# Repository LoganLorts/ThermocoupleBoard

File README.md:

Current iteration uses an Arduino giga with an arduino mega data shield communicating with the LTC2984.
Links:
https://www.analog.com/en/products/ltc2984.html
https://store-usa.arduino.cc/products/giga-r1-wifi?srsltid=AfmBOopj3Obfn5Uupg23lJG5jRPGHVTn0Cs4W42ruEa2sTFBW0iU7hsE
https://learn.adafruit.com/adafruit-data-logger-shield/overview
https://www.analog.com/en/resources/evaluation-hardware-and-software/evaluation-boards-kits/dc2420a.html#eb-overview (demo board)

To Do:

Software:
All software currently made for demo board, once the new LTC2984 (thermocouple board) is completed, adapt code.

harmonic boundry heating:
test heating accuracy
test acquisition rate
test timing of loop
parallelize processes
make LTC get measurements while the rest of the loop runs

ATMC LTC2984:
test heating accuracy
test acquisition rate
test timing of loop
parallelize processes
make LTC get measurements while the rest of the loop runs

Hardware:

Thermocouple board:
Test functionality and accuracy
solder termblocks

Heating Board:
order and solder logic inverters
order and solder optoisolaters
order and solder heating termblocks
testing

giga hat:
(if needed) Once thermocouple and heating board are tested, make giga hat for SD card reader, mosfet drives, thermocouple SPI connections, humidity sensor, and pressure sensor

Demo board:
Order and solder 2 of the remaining heating termblocks and mosfet drivers (currently one working)
3d print case
rewire to clean setup around the case
(optional) Add barrel jack connector for power

Notes:

Demo board notes:
mosfet driver pin: pin 8
LTC chip select pin: pin 7
SD card reader chip select: pin 10
Power from DC power supply up to 15V
serial speed: 115200
Cold junction sensor avaliable on channel 1 and channel 2 (only need one)
Differential thermocouple readings, select higher channel with differential setting; the postive lead goes to the higher channel and negative lead to one channel lower.
Intented to run up to 9 thermocouples with 3 mosfet drivers runnning the heating element.
Real time clock is I2C on wire 1 (address 0x68)
cold junction sensor is an npn BJT shorted to function as a diode, the ideality factor can be changed to reflect this, but default works.

SPI connections are shown here, ribbon cable connector is not used with the giga. 

Heating board notes:
rated 15V 10 Amps (realistically no more than 5 amps with 3 drivers on)
Do not common ground with the giga

Thermocouple board notes:
Cold junction sensor avaliable on channel 20 and channel 9. Use channel 20 to normalize channels 14-19, channel 9 for the rest.
Intended to run 18 thermocouples, single ended mode (thermocouples go channel to ground)
cold junction sensor is an npn BJT shorted to function as a diode, the ideality factor can be changed to reflect this, but default works.

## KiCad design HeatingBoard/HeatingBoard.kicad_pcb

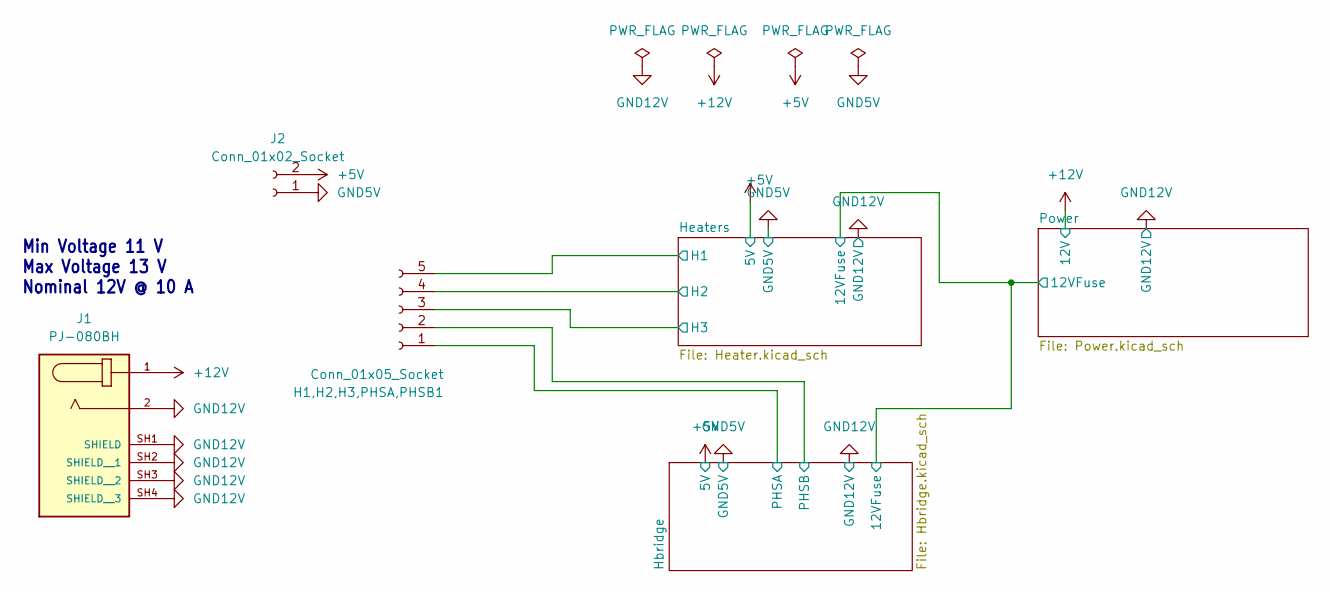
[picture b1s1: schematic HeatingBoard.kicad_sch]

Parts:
H1,H2,H3,PHSA,PHSB1: Conn_01x05_Socket; PinHeader_1x05_P2.54mm_Vertical
J1: PJ-080BH; CUI_PJ-080BH; PARTREV 1.04
J2: Conn_01x02_Socket; PinHeader_1x02_P2.54mm_Vertical

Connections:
+5V: J2.2; also elsewhere on the board
+12V: J1.1; also elsewhere on the board
/Hbridge/PHSA: H1,H2,H3,PHSA,PHSB1.1; also elsewhere on the board
/Hbridge/PHSB: H1,H2,H3,PHSA,PHSB1.2; also elsewhere on the board
/Heaters/H1: H1,H2,H3,PHSA,PHSB1.5; also elsewhere on the board
/Heaters/H2: H1,H2,H3,PHSA,PHSB1.4; also elsewhere on the board
/Heaters/H3: H1,H2,H3,PHSA,PHSB1.3; also elsewhere on the board
GND5V: J2.1; also elsewhere on the board
GND12V: J1.2, J1.SH1 (SHIELD), J1.SH2 (SHIELD__1), J1.SH3 (SHIELD__2), J1.SH4 (SHIELD__3); also elsewhere on the board

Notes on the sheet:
Min Voltage 11 V Max Voltage 13 V Nominal 12V @ 10 A

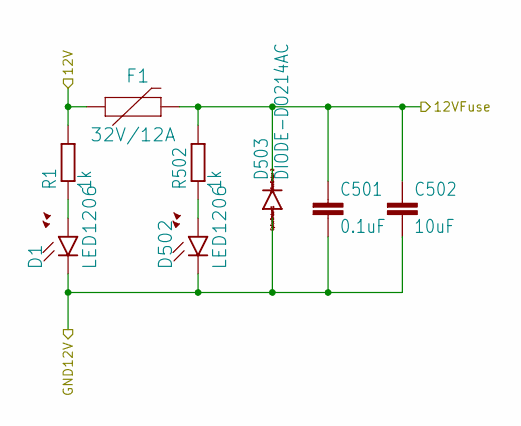
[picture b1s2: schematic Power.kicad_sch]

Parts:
C501: 0.1uF; C1206
C502: 10uF; C1206
D1, D502: LED1206; LED-1206
D503: DIODE-DO214AC; DO214AC_210; DIGI-PN SMAZ15-TPMSCT-ND
F1: 32V/12A; 1206; DIGI-PN 283-2805-1-ND
R1, R502: 1k; R1206

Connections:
+12V: F1.1, R1.2; also elsewhere on the board
/Hbridge/12VFuse: C501.1, C502.1, D503.C, F1.2, R502.2; also elsewhere on the board
GND12V: C501.2, C502.2, D1.C, D502.C, D503.A; also elsewhere on the board
unnamed: D1.A, R1.1
unnamed: D502.A, R502.1

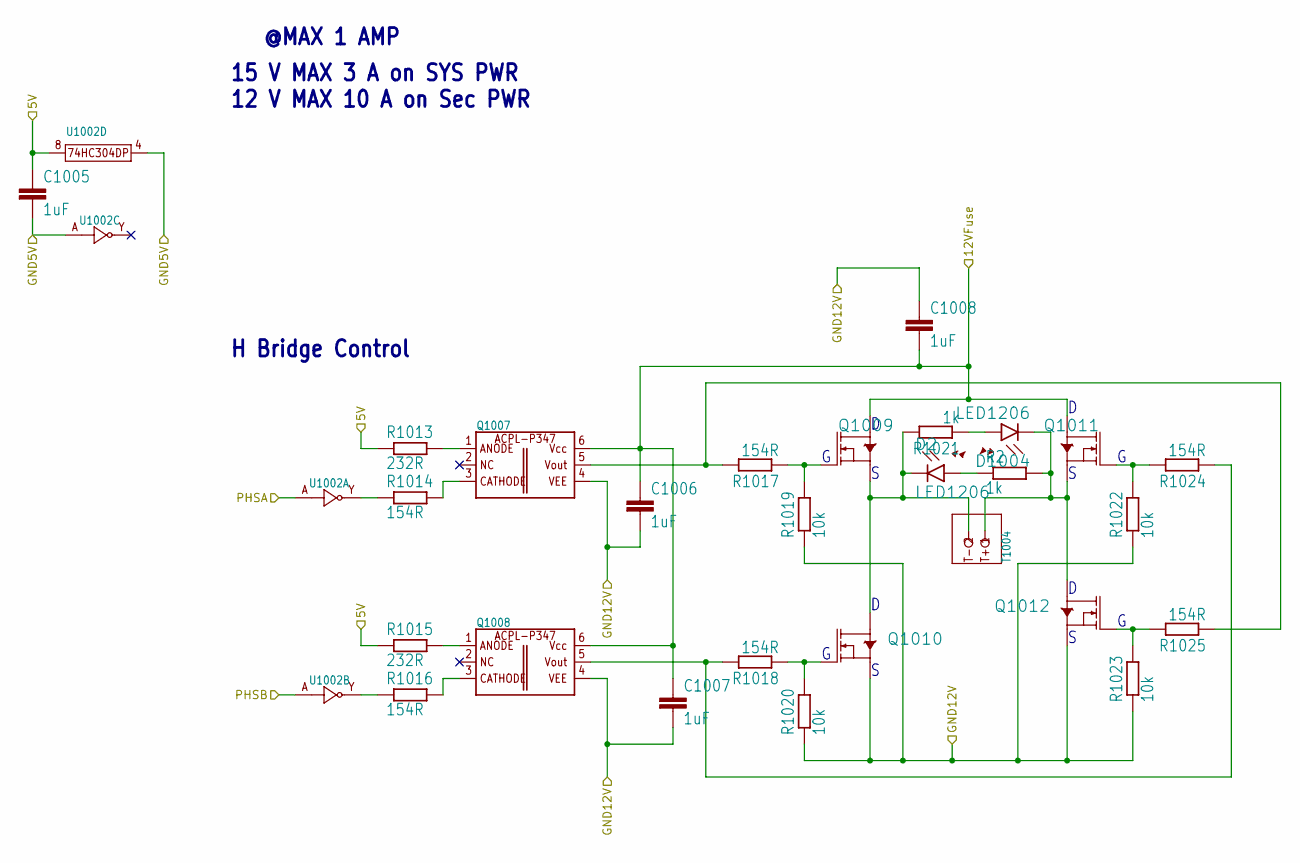
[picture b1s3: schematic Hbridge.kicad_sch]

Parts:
C1005, C1006, C1007, C1008: 1uF; C1206
D2, D1004: LED1206; LED-1206
Q1007, Q1008: ACPL-P347; SO-6W
Q1009, Q1010, Q1011, Q1012: N-MOSFETT0252; TO252
R2, R1021: 1k; R1206
R1013, R1015: 232R; R1206
R1014, R1016, R1017, R1018, R1024, R1025: 154R; R1206
R1019, R1020, R1022, R1023: 10k; R1206
T1004: CON3.81; 2CONN(3.81MM)
U1002: NOT(3)TSSOP8; TSSOP-8

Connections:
+5V: C1005.1, R1013.1, R1015.1, U1002.8; also elsewhere on the board
/Hbridge/12VFuse: C1006.1, C1007.1, C1008.2, Q1007.6, Q1008.6, Q1009.D, Q1011.D; also elsewhere on the board
/Hbridge/PHSA: U1002.1 (A); also elsewhere on the board
/Hbridge/PHSB: U1002.3 (A); also elsewhere on the board
GND5V: C1005.2, U1002.4, U1002.6 (A); also elsewhere on the board
GND12V: C1006.2, C1007.2, C1008.1, Q1007.4, Q1008.4, Q1010.S, Q1012.S, R1019.1, R1020.1, R1022.1, R1023.1; also elsewhere on the board
unnamed: D2.A, R2.1
unnamed: D2.C, Q1009.S, Q1010.D, R1021.2, T1004.2
unnamed: D1004.A, R1021.1
unnamed: D1004.C, Q1011.S, Q1012.D, R2.2, T1004.1
unnamed: Q1007.1, R1013.2
unnamed: Q1007.3, R1014.2
unnamed: Q1007.5, R1017.2, R1025.1
unnamed: Q1008.1, R1015.2
unnamed: Q1008.3, R1016.2
unnamed: Q1008.5, R1018.2, R1024.1
unnamed: Q1009.G, R1017.1, R1019.2
unnamed: Q1010.G, R1018.1, R1020.2
unnamed: Q1011.G, R1022.2, R1024.2
unnamed: Q1012.G, R1023.2, R1025.2
unnamed: R1014.1, U1002.7 (Y)
unnamed: R1016.1, U1002.5 (Y)

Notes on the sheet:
15 V MAX 3 A on SYS PWR 12 V MAX 10 A on Sec PWR
@MAX 1 AMP
H Bridge Control

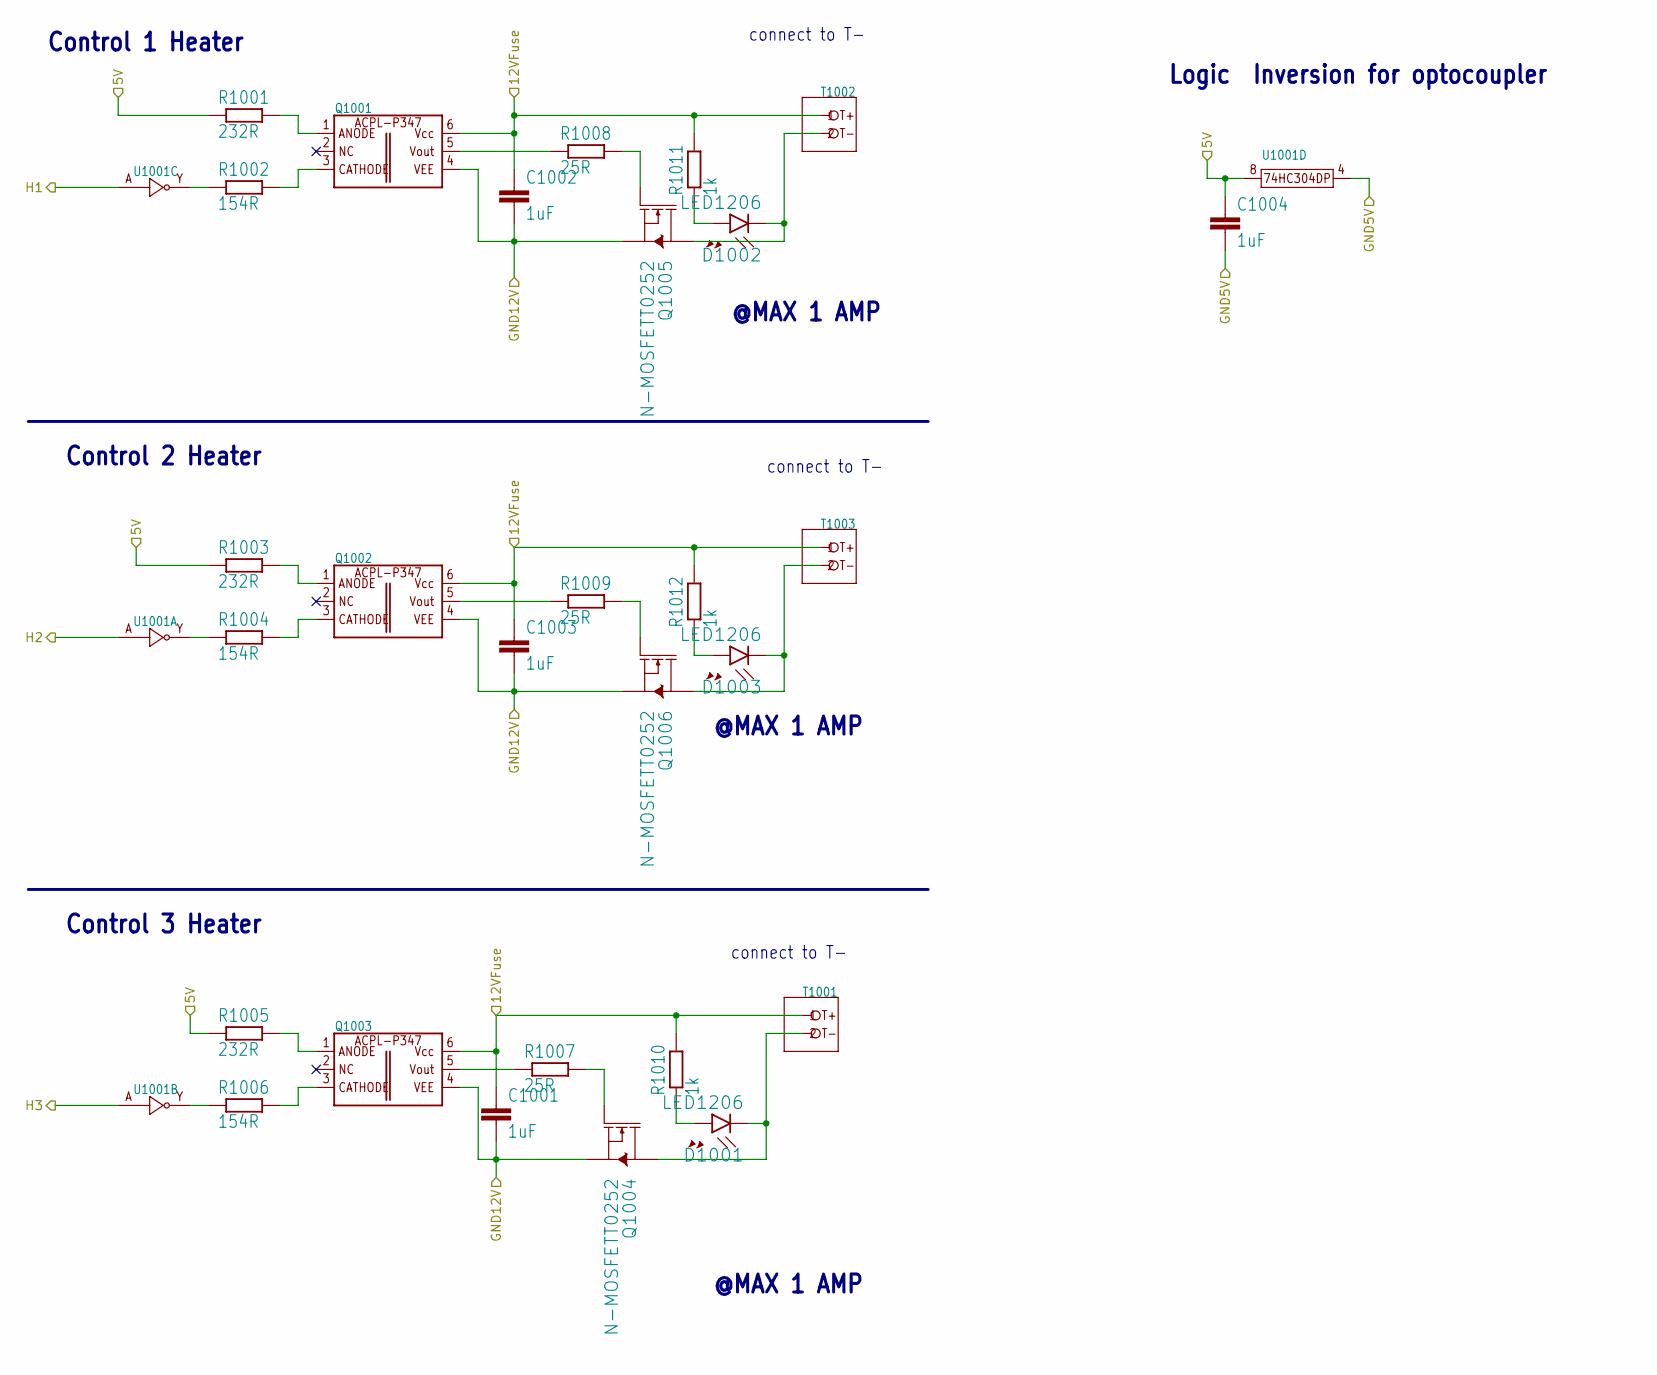
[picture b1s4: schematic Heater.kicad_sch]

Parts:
C1001, C1002, C1003, C1004: 1uF; C1206
D1001, D1002, D1003: LED1206; LED-1206
Q1001, Q1002, Q1003: ACPL-P347; SO-6W
Q1004, Q1005, Q1006: N-MOSFETT0252; TO252
R1001, R1003, R1005: 232R; R1206
R1002, R1004, R1006: 154R; R1206
R1007, R1008, R1009: 25R; R1206
R1010, R1011, R1012: 1k; R1206
T1001, T1002, T1003: CON3.81; 2CONN(3.81MM)
U1001: NOT(3)TSSOP8; TSSOP-8

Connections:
+5V: C1004.1, R1001.1, R1003.1, R1005.1, U1001.8; also elsewhere on the board
/Hbridge/12VFuse: C1001.1, C1002.1, C1003.1, Q1001.6, Q1002.6, Q1003.6, R1010.2, R1011.2, R1012.2, T1001.1, T1002.1, T1003.1; also elsewhere on the board
/Heaters/H1: U1001.6 (A); also elsewhere on the board
/Heaters/H2: U1001.1 (A); also elsewhere on the board
/Heaters/H3: U1001.3 (A); also elsewhere on the board
GND5V: C1004.2, U1001.4; also elsewhere on the board
GND12V: C1001.2, C1002.2, C1003.2, Q1001.4, Q1002.4, Q1003.4, Q1004.S, Q1005.S, Q1006.S; also elsewhere on the board
unnamed: D1001.A, R1010.1
unnamed: D1001.C, Q1004.D, T1001.2
unnamed: D1002.A, R1011.1
unnamed: D1002.C, Q1005.D, T1002.2
unnamed: D1003.A, R1012.1
unnamed: D1003.C, Q1006.D, T1003.2
unnamed: Q1001.1, R1001.2
unnamed: Q1001.3, R1002.2
unnamed: Q1001.5, R1008.1
unnamed: Q1002.1, R1003.2
unnamed: Q1002.3, R1004.2
unnamed: Q1002.5, R1009.1
unnamed: Q1003.1, R1005.2
unnamed: Q1003.3, R1006.2
unnamed: Q1003.5, R1007.1
unnamed: Q1004.G, R1007.2
unnamed: Q1005.G, R1008.2
unnamed: Q1006.G, R1009.2
unnamed: R1004.1, U1001.7 (Y)
unnamed: R1006.1, U1001.5 (Y)
unnamed: R1002.1, U1001.2 (Y)

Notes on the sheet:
Logic Inversion for optocoupler
Control 3 Heater
@MAX 1 AMP
connect to T-
Control 2 Heater
Control 1 Heater

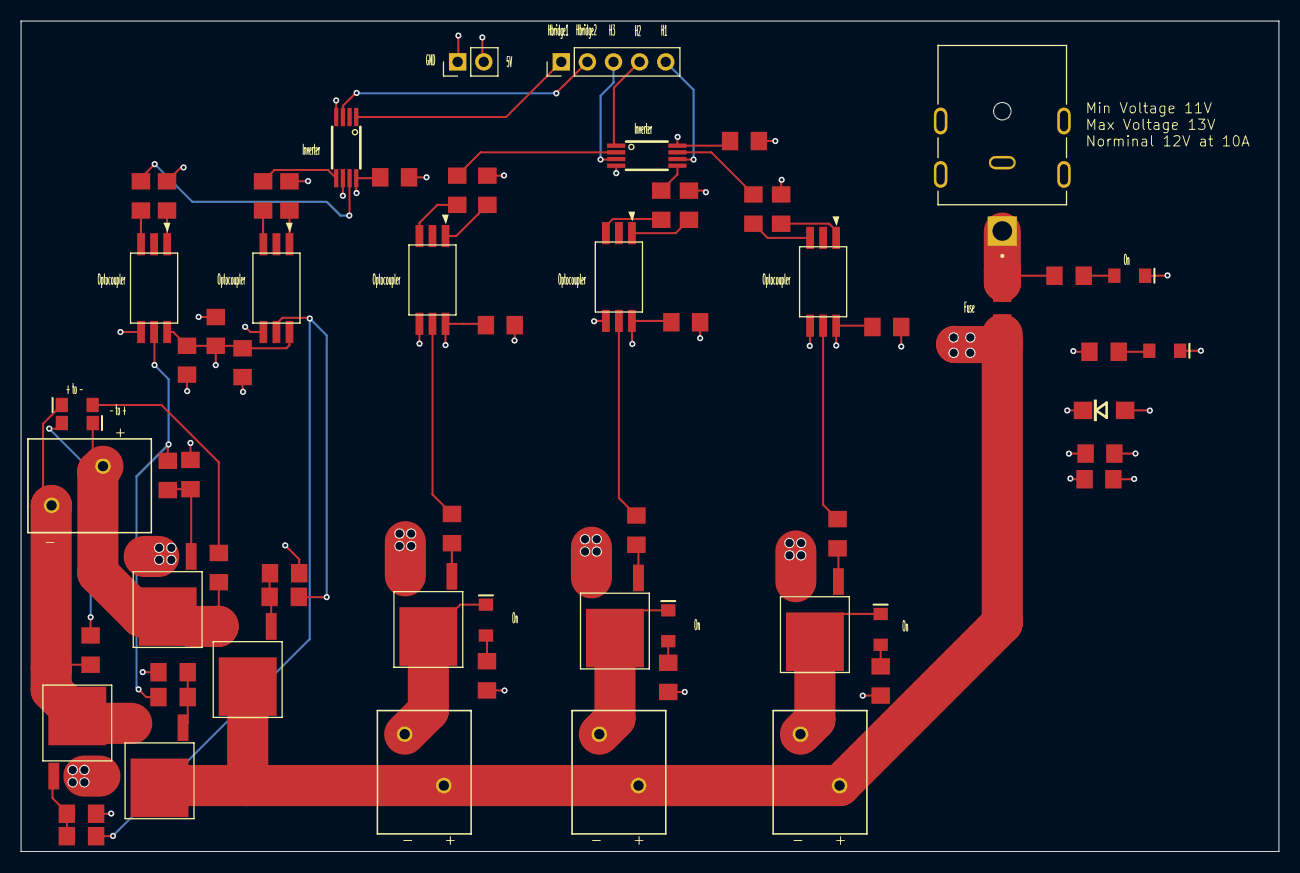
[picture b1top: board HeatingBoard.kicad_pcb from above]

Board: 4 copper layers, 122.4 x 80.8 mm, 68 parts (0 on the bottom side), 49 nets.

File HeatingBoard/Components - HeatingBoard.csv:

Reference,Qty,Value,DNP,Exclude from BOM,Exclude from Board,Footprint,Datasheet
C501,1,0.1uF X79,,,,Power:C1206,
C502,1,10uF X79,,,,Power:C1206,
"C1001,C1002,C1003,C1004,C1005,C1006,C1007,C1008",8,1uF X79,,,,Power:C1206,
"D1,D2,D502,D1001,D1002,D1003,D1004",7,LED1206,,,,Power:LED-1206,
D503,1,DIODE-DO214AC,,,,TVSdiode:DO214AC_210,
F1,1,32V/12A,,,,Power:1206,
"H1,H2,H3,PHSA,PHSB1",1,Conn_01x05_Socket,,,,Connector_PinHeader_2.54mm:PinHeader_1x05_P2.54mm_Vertical,~
J1,1,PJ-080BH,,,,Connector_BarrelJack:CUI_PJ-080BH,
J2,1,Conn_01x02_Socket,,,,Connector_PinHeader_2.54mm:PinHeader_1x02_P2.54mm_Vertical,~
"Q1001,Q1002,Q1003,Q1007,Q1008",5,ACPL-P347,,,,Power:SO-6W,
"Q1004,Q1005,Q1006,Q1009,Q1010,Q1011,Q1012",7,N-MOSFETT0252,,,,Power:TO252,
"R1,R2,R502,R1010,R1011,R1012,R1021",7,1k,,,,Power:R1206,
"R1001,R1003,R1005,R1013,R1015",5,232R,,,,Power:R1206,
"R1002,R1004,R1006,R1014,R1016,R1018,R1024,R1025",8,154R,,,,Power:R1206,
"R1007,R1008,R1009,R1017",4,25R,,,,Power:R1206,
"R1019,R1020,R1022,R1023",4,10k,,,,Power:R1206,
"T1001,T1002,T1003,T1004",4,CON3.81,,,,Power:2CONN(3.81MM),
"U1001,U1002",2,NOT(3)TSSOP8,,,,Power:TSSOP-8,

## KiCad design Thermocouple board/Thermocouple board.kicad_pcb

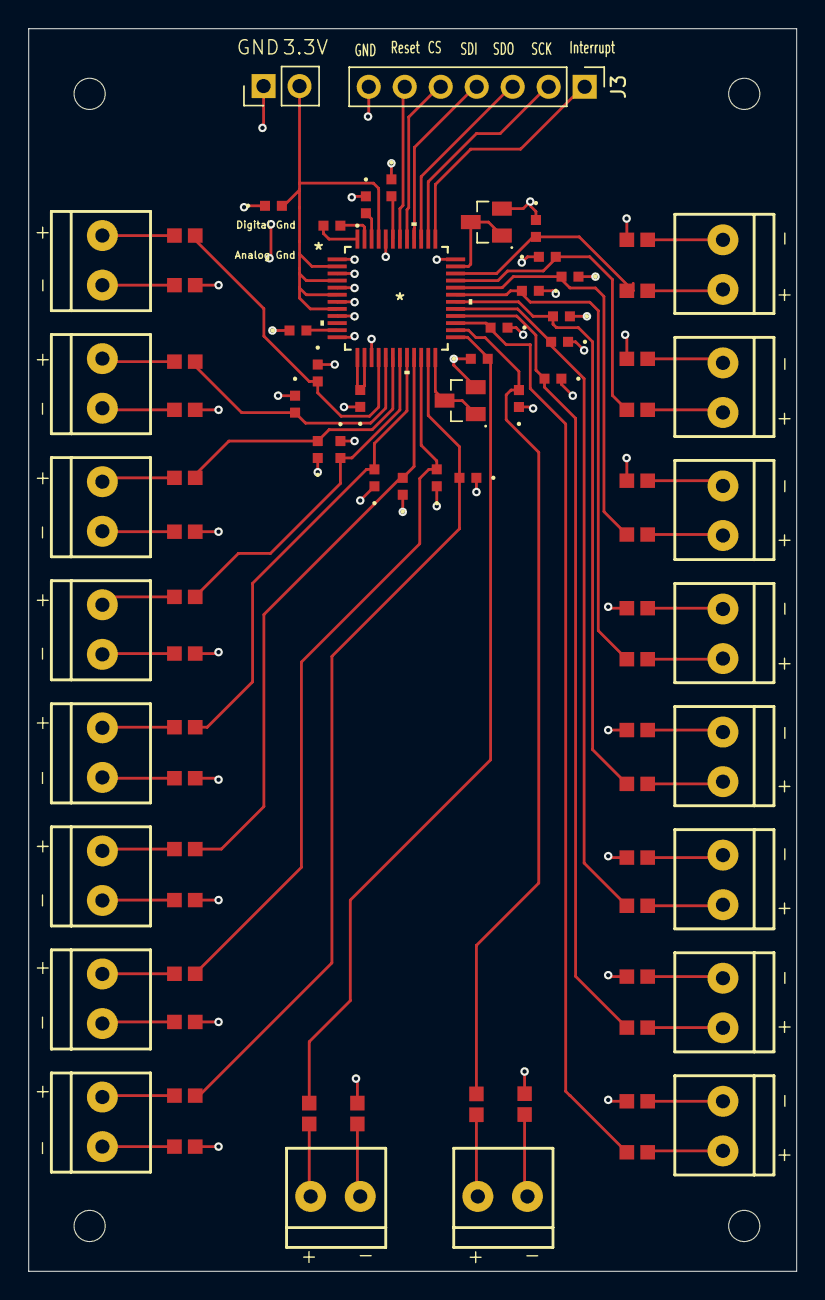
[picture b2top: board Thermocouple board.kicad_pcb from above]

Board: 2 copper layers, 54.2 x 87.7 mm, 83 parts (0 on the bottom side), 70 nets.

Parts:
C1, C4, C5, C6, C7, C8, C9, C10, C11, C16, C17, C18, C19, C20, C21, C22, C23, C24, C26: .1 μF; CAP_GRM155R61A106ME11_MUR_0402
C2, C3: 1 μF; CAP_GRM155R61A106ME11_MUR_0402
C13, C14, C15: 10 μF; CAP_GRM155R61A106ME11_MUR_0402
J2: Conn_01x02_Pin; PinHeader_1x02_P2.54mm_Vertical
J3: Conn_01x07_Socket; PinHeader_1x07_P2.54mm_Vertical
Q1, Q2: MMBT3904LT1G; SOT95P240X111-3N
R1, R2, R3, R4, R5, R6, R7, R8, R9, R10, R11, R12, R13, R14, R15, R16, R17, R18, R19, R20, R21, R22, R23, R24, R25, R26, R27, R28, R29, R30, R31, R32, R33, R34, R35, R36: 100 ohm; RESC1607X60N
U1: LTC2984CLX-PBF; LQFP-48_LX_LIT
X1, X2, X3, X4, X5, X6, X7, X8, X9, X10, X11, X12, X13, X14, X15, X16, X17, X18: TERMBLOCK_1X2-3.5MM

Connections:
+3.3V: C1.2, J2.2, U1.2 (VDD), U1.4 (VDD), U1.6 (VDD), U1.8 (VDD), U1.45 (VDD)
/Channel1: C7.2, R7.2, U1.16 (CH1)
/Channel2: C4.2, R1.2, U1.17 (CH2)
/Channel3: C5.2, R3.2, U1.18 (CH3)
/Channel4: C6.2, R5.2, U1.19 (CH4)
/Channel5: C8.2, R9.2, U1.20 (CH5)
/Channel6: C9.2, R11.2, U1.21 (CH6)
/Channel7: C10.2, R13.2, U1.22 (CH7)
/Channel8: C11.2, R15.2, U1.23 (CH8)
/Channel9: Q1.1 (B), Q1.3 (C), U1.24 (CH9)
/Channel10: C17.2, R17.2, U1.25 (CH10)
/Channel11: C18.2, R19.2, U1.26 (CH11)
/Channel12: C19.2, R21.2, U1.27 (CH12)
/Channel13: C20.2, R23.2, U1.28 (CH13)
/Channel14: C21.2, R25.2, U1.29 (CH14)
/Channel15: C22.2, R27.2, U1.30 (CH15)
/Channel16: C23.2, R29.2, U1.31 (CH16)
/Channel17: C24.2, R31.2, U1.32 (CH17)
/Channel18: C16.2, R33.2, U1.33 (CH18)
/Channel19: C26.2, R35.2, U1.34 (CH19)
/Channel20: Q2.1 (B), Q2.3 (C), U1.35 (CH20)
GND: C1.1, C2.1, C3.1, C4.1, C5.1, C6.1, C7.1, C8.1, C9.1, C10.1, C11.1, C14.1, C15.1, C16.1, C17.1, C18.1, C19.1, C20.1, C21.1, C22.1, C23.1, C24.1, C26.1, J2.1, J3.7, Q1.2 (E), Q2.2 (E), R2.2, R4.2, R6.2, R8.2, R10.2, R12.2, R14.2, R16.2, R18.2, R20.2, R22.2, R24.2, R26.2, R28.2, R30.2, R32.2, R34.2, R36.2, U1.1 (GND), U1.3 (GND), U1.5 (GND), U1.7 (GND), U1.9 (GND), U1.12 (GND), U1.15 (GND), U1.36 (COM), U1.44 (GND)
unnamed: J3.1, U1.37 (INTERRUPT)
unnamed: J3.2, U1.38 (SCK)
unnamed: J3.3, U1.39 (SDO)
unnamed: J3.4, U1.40 (SDI)
unnamed: J3.5, U1.41 (*CS)
unnamed: J3.6, U1.42 (*RESET)
unnamed: R1.1, X2.2
unnamed: R2.1, X2.1
unnamed: R3.1, X3.2
unnamed: R4.1, X3.1
unnamed: R5.1, X4.2
unnamed: R6.1, X4.1
unnamed: R7.1, X1.2
unnamed: R8.1, X1.1
unnamed: R9.1, X5.2
unnamed: R10.1, X5.1
unnamed: R11.1, X6.2
unnamed: R12.1, X6.1
unnamed: R13.1, X7.2
unnamed: R14.1, X7.1
unnamed: R15.1, X8.2
unnamed: R16.1, X8.1
unnamed: R17.1, X9.2
unnamed: R18.1, X9.1
unnamed: R19.1, X10.2
unnamed: R20.1, X10.1
unnamed: R21.1, X11.2
unnamed: R22.1, X11.1
unnamed: R23.1, X12.2
unnamed: R24.1, X12.1
unnamed: R25.1, X13.2
unnamed: R26.1, X13.1
unnamed: R27.1, X14.2
unnamed: R28.1, X14.1
unnamed: R29.1, X15.2
unnamed: R30.1, X15.1
unnamed: R31.1, X16.2
unnamed: R32.1, X16.1
unnamed: R33.1, X17.2
unnamed: R34.1, X17.1
unnamed: R35.1, X18.2
unnamed: R36.1, X18.1
unnamed: C15.2, U1.43 (LDO)
unnamed: C13.2, U1.48 (Q1)
unnamed: C13.1, U1.47 (Q2)
unnamed: C14.2, U1.46 (Q3)
unnamed: C2.2, U1.13 (VREFOUT), U1.14 (VREFP)
unnamed: C3.2, U1.11 (VREF_BYP)

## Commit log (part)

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2026-02-26 Add files via upload
    Added thermocouple footprints
2026-03-24 Add files via upload
    Add Heating Board
2026-04-03 Add files via upload
    Fix H-bridge Resistor Value
